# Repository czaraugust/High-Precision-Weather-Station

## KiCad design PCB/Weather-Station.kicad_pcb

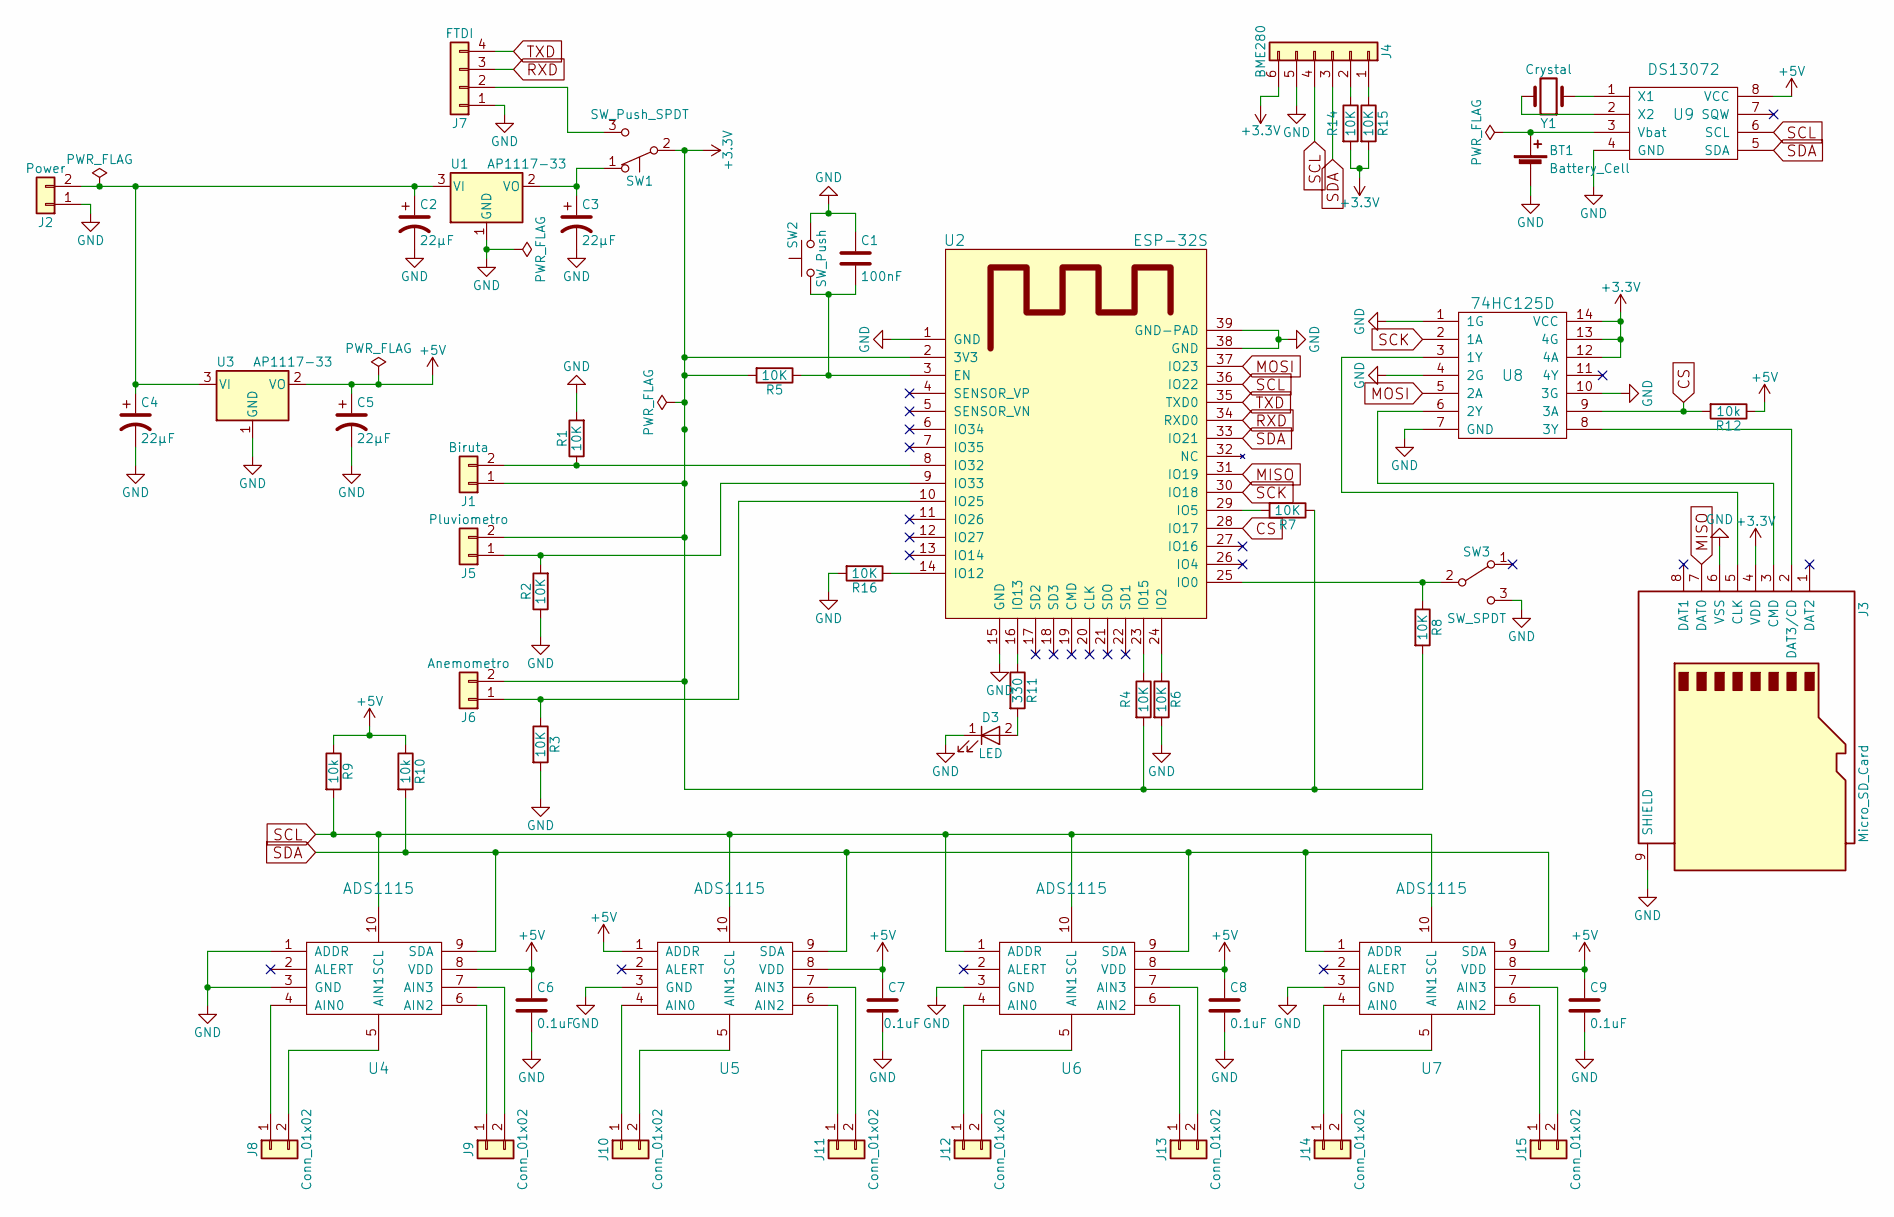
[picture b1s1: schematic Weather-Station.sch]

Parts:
BT1: Battery_Cell; Keystone_3000_1x12mm-CoinCell
C1: 100nF; C_0805
C2, C3, C4, C5: 22μF; CP_Elec_6.3x7.7
C6, C7, C8, C9: 0.1uF; C_0805
D3: LED; LED_0805
J1: Biruta; TerminalBlock_Phoenix_MPT-2.54mm_2pol
J2: Power; TerminalBlock_Phoenix_PT-3.5mm_2pol
J3: Micro_SD_Card; Conn_uSDcard
J4: BME280; TerminalBlock_Phoenix_MPT-2.54mm_6pol
J5: Pluviometro; TerminalBlock_Phoenix_MPT-2.54mm_2pol
J6: Anemometro; TerminalBlock_Phoenix_MPT-2.54mm_2pol
J7: FTDI; Pin_Header_Straight_1x04_Pitch2.54mm
J8, J9, J10, J11, J12, J13, J14, J15: Conn_01x02; TerminalBlock_Phoenix_MPT-2.54mm_2pol
R1, R2, R3, R4, R5, R6, R7, R8, R14, R15, R16: 10K; R_0805
R9, R10, R12: 10k; R_0805
R11: 330; R_0805
SW1: SW_Push_SPDT; SW_Micro_SPST
SW2: SW_Push; SW_PUSH_6mm
SW3: SW_SPDT; SW_Micro_SPST
U1, U3: AP1117-33; SOT-223
U2: ESP-32S; ESP32-WROOM
U4, U5, U6, U7: ADS1115; MSOP-10_3x3mm_Pitch0.5mm
U8: 74HC125D; SOIC-14_3.9x8.7mm_Pitch1.27mm
U9: DS13072; SOIC-8_3.9x4.9mm_Pitch1.27mm
Y1: Crystal; Crystal_DS15_d1.5mm_l5.0mm_Horizontal

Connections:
+3V3: J1.1, J3.4 (VDD), J4.6, J5.2, J6.2, R4.2, R5.2, R7.1, R8.2, R14.2, R15.2, SW1.2 (B), U2.2 (3V3), U8.12 (4A), U8.13 (4G), U8.14 (VCC); also elsewhere on the board
+5V: C5.1, C6.1, C7.1, C8.1, C9.1, R9.1, R10.1, R12.1, U3.2 (VO), U4.8 (VDD), U5.1 (ADDR), U5.8 (VDD), U6.8 (VDD), U7.8 (VDD), U9.8 (VCC)
CS: R12.2, U2.28 (IO17), U8.9 (3A)
GND: BT1.2 (-), C1.1, C2.2, C3.2, C4.2, C5.2, C6.2, C7.2, C8.2, C9.2, D3.1 (K), J2.1, J3.6 (VSS), J3.9 (SHIELD), J4.5, J7.1, R1.2, R2.1, R3.2, R6.2, R16.2, SW2.2, SW3.3 (C), U1.1 (GND), U2.1 (GND), U2.15 (GND), U2.38 (GND), U2.39 (GND-PAD), U3.1 (GND), U4.1 (ADDR), U4.3 (GND), U5.3 (GND), U6.3 (GND), U7.3 (GND), U8.1 (1G), U8.4 (2G), U8.7 (GND), U8.10 (3G), U9.4 (GND); also elsewhere on the board
MISO: J3.7 (DAT0), U2.31 (IO19)
MOSI: U2.37 (IO23), U8.5 (2A)
unnamed: BT1.1 (+), U9.3 (Vbat)
unnamed: C1.2, R5.1, SW2.1, U2.3 (EN)
unnamed 8: C2.1, C4.1, J2.2, U1.3 (VI), U3.3 (VI); also elsewhere on the board
unnamed: C3.1, SW1.1 (A), U1.2 (VO)
unnamed: D3.2 (A), R11.2
unnamed 11: J1.2, R1.1, U2.8 (IO32); also elsewhere on the board
unnamed: J3.2 (DAT3/CD), U8.8 (3Y)
unnamed: J3.3 (CMD), U8.6 (2Y)
unnamed: J3.5 (CLK), U8.3 (1Y)
unnamed: J4.1, R15.1
unnamed: J4.2, R14.1
unnamed 17: J5.1, R2.2, U2.9 (IO33); also elsewhere on the board
unnamed 18: J6.1, R3.1, U2.10 (IO25); also elsewhere on the board
unnamed: J7.2, SW1.3 (C)
unnamed: J8.1, U4.4 (AIN0)
unnamed: J8.2, U4.5 (AIN1)
unnamed: J9.1, U4.6 (AIN2)
unnamed: J9.2, U4.7 (AIN3)
unnamed: J10.1, U5.4 (AIN0)
unnamed: J10.2, U5.5 (AIN1)
unnamed: J11.1, U5.6 (AIN2)
unnamed: J11.2, U5.7 (AIN3)
unnamed: J12.1, U6.4 (AIN0)
unnamed: J12.2, U6.5 (AIN1)
unnamed: J13.1, U6.6 (AIN2)
unnamed: J13.2, U6.7 (AIN3)
unnamed: J14.1, U7.4 (AIN0)
unnamed: J14.2, U7.5 (AIN1)
unnamed: J15.1, U7.6 (AIN2)
unnamed: J15.2, U7.7 (AIN3)
unnamed: R4.1, U2.23 (IO15)
unnamed: R6.1, U2.24 (IO2)
unnamed: R7.2, U2.29 (IO5)
unnamed: R8.1, SW3.2 (B), U2.25 (IO0)
unnamed: R11.1, U2.16 (IO13)
unnamed: R16.1, U2.14 (IO12)
unnamed: U9.1 (X1), Y1.1
unnamed: U9.2 (X2), Y1.2
RXD: J7.3, U2.34 (RXD0)
SCK: U2.30 (IO18), U8.2 (1A)
SCL: J4.4, R9.2, U2.36 (IO22), U4.10 (SCL), U5.10 (SCL), U6.1 (ADDR), U6.10 (SCL), U7.10 (SCL), U9.6 (SCL)
SDA: J4.3, R10.2, U2.33 (IO21), U4.9 (SDA), U5.9 (SDA), U6.9 (SDA), U7.1 (ADDR), U7.9 (SDA), U9.5 (SDA)
TXD: J7.4, U2.35 (TXD0)

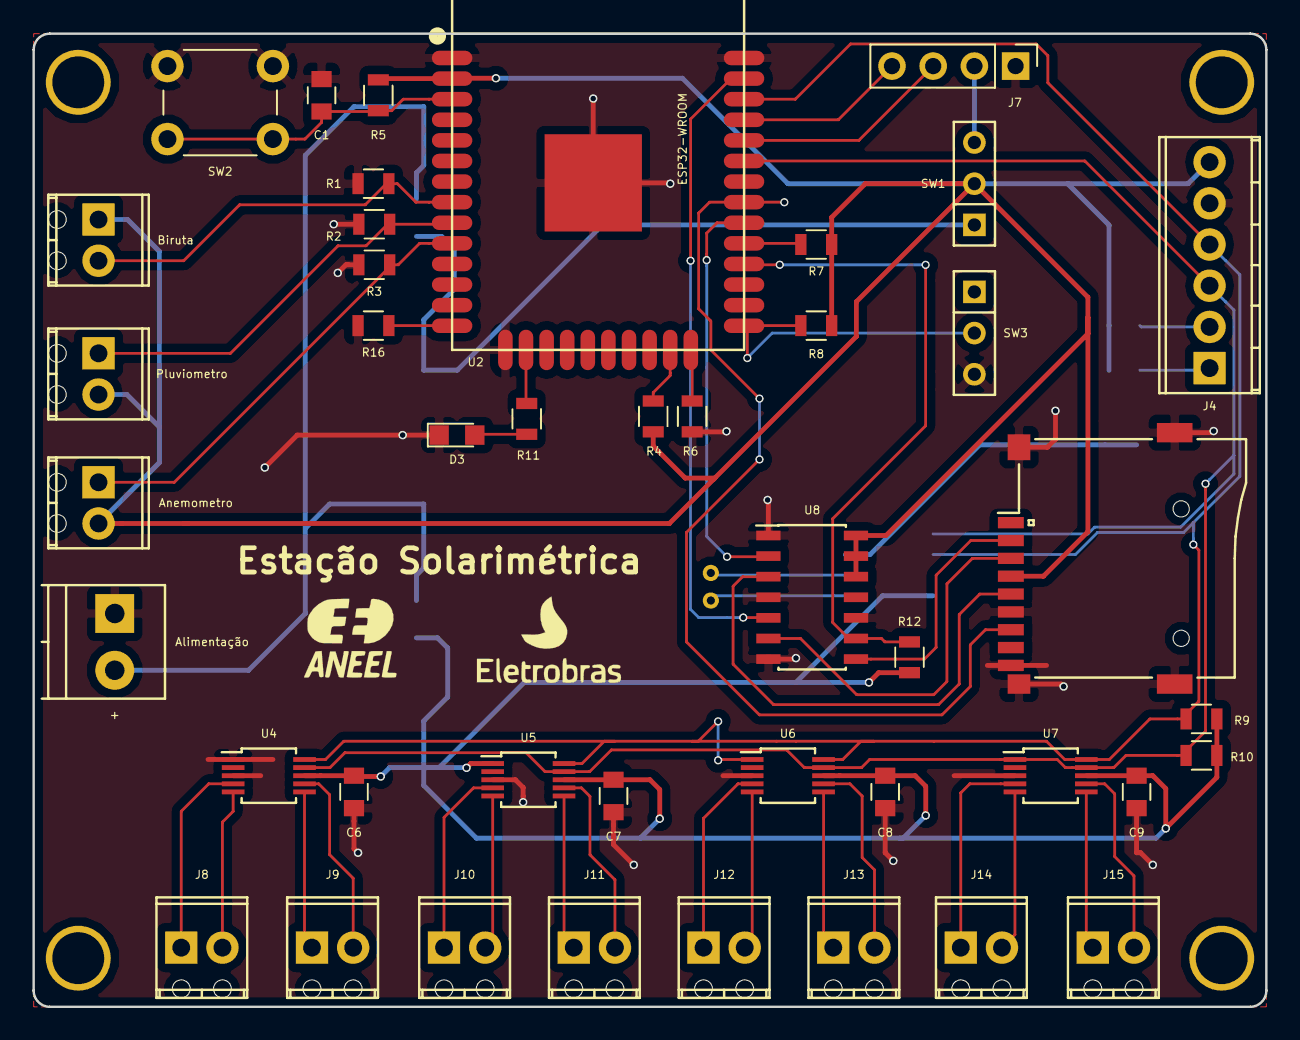
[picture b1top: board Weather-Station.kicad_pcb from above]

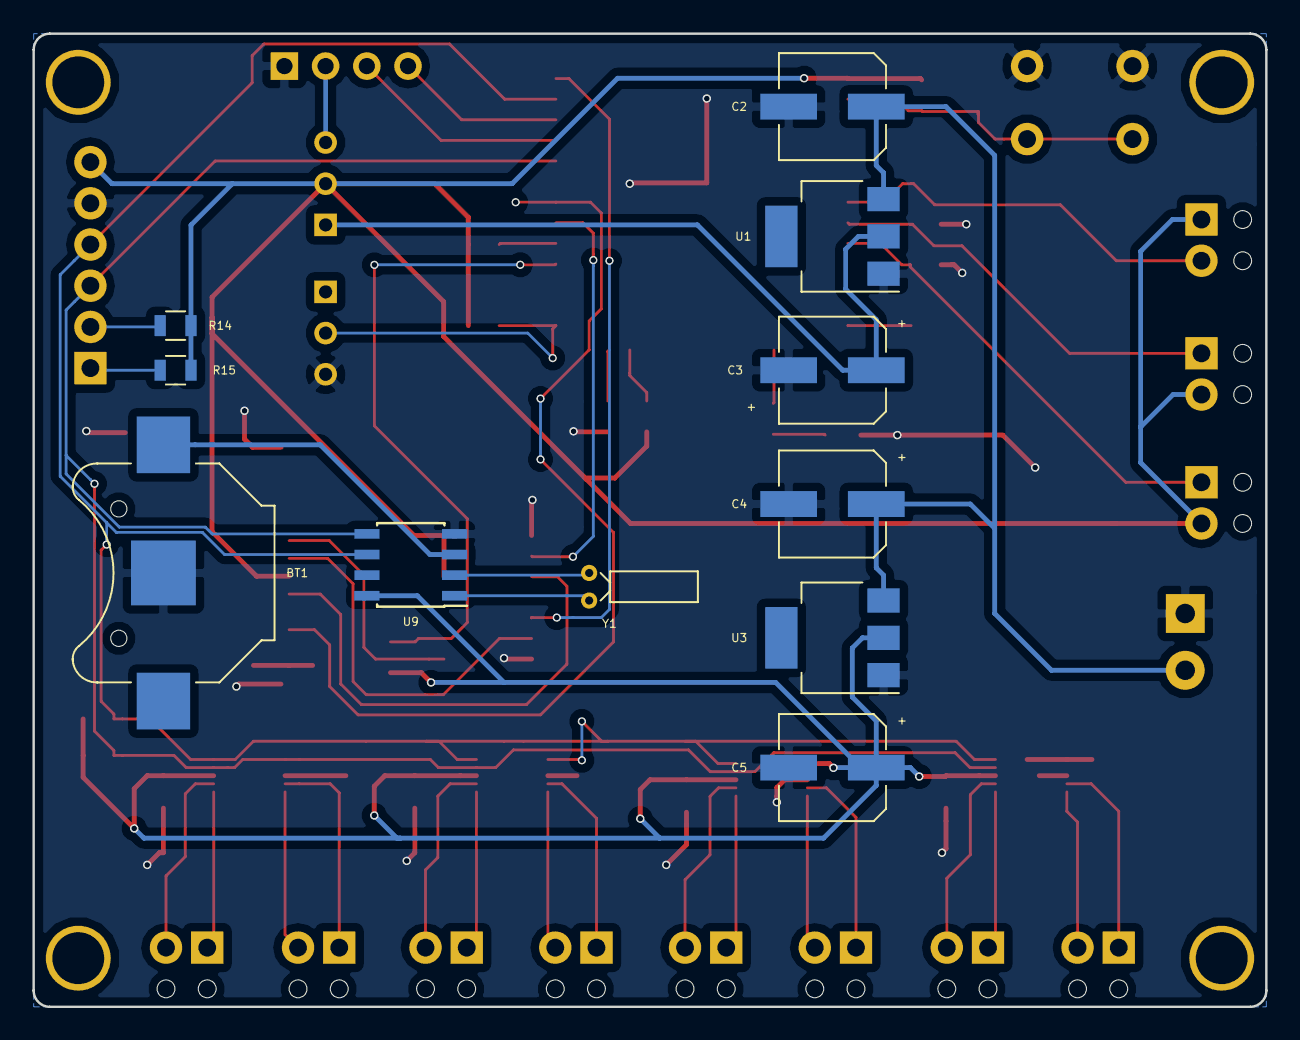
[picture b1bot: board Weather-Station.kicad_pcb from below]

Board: 2 copper layers, 76.0 x 60.0 mm, 54 parts (11 on the bottom side), 49 nets.

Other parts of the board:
Alimentação: Power; TerminalBlock_Phoenix_PT-3.5mm_2pol
Anemometro: Anemometro; TerminalBlock_Phoenix_MPT-2.54mm_2pol
Biruta: Biruta; TerminalBlock_Phoenix_MPT-2.54mm_2pol
Pluviometro: Pluviometro; TerminalBlock_Phoenix_MPT-2.54mm_2pol

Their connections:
+3V3: Anemometro.2, Biruta.1, Pluviometro.2; also elsewhere on the board
GND: Alimentação.1; also elsewhere on the board
unnamed 8: Alimentação.2; also elsewhere on the board
unnamed 11: Biruta.2; also elsewhere on the board
unnamed 17: Pluviometro.1; also elsewhere on the board
unnamed 18: Anemometro.1; also elsewhere on the board

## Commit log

2017-10-06 Starting
2018-01-03 Adding pressure, temperature and humidity sensor
2018-01-05 Adicinando código do ESP
2018-01-05 Adding luximeter
2018-01-05 Starting merge of sensors
2018-01-09 Putting all sensors together
2018-01-09 Adicionado sensor de direção do vento
2018-01-10 Finalizing day
2018-01-12 Adicionando esquematico
2018-01-12 Initializing MQTT
2018-01-15 Adicionando Gerber
2018-01-16 Refazendo PCB
2018-02-20 Finalizing
2018-03-05 Ajustando os valores da biruta
2018-03-13 Starting communicate with RPi
2018-03-13 Adding PCB
2018-08-01 Iniciada a PCB com ESP32 devkit
2018-08-01 Tirando o circuito de programação do ESP
2018-08-02 Feita a PCB com ESP32 devkit
2018-08-31 Alterando as PCBs da estação para usar os ADCs e o DataLogger
2018-08-31 Iniciado PCB
2018-08-31 Fazendo pcb
2018-09-02 Finalizando PCB
2018-09-03 Ajustando PCB
2018-09-05 Ajustando PCBs
2018-09-05 Adicionando gerbers
2018-09-17 Colocando mountholes e silkscreens
2018-09-19 Adicionando componentes do data logger
2018-09-21 Fazendo PCB com o data logger
